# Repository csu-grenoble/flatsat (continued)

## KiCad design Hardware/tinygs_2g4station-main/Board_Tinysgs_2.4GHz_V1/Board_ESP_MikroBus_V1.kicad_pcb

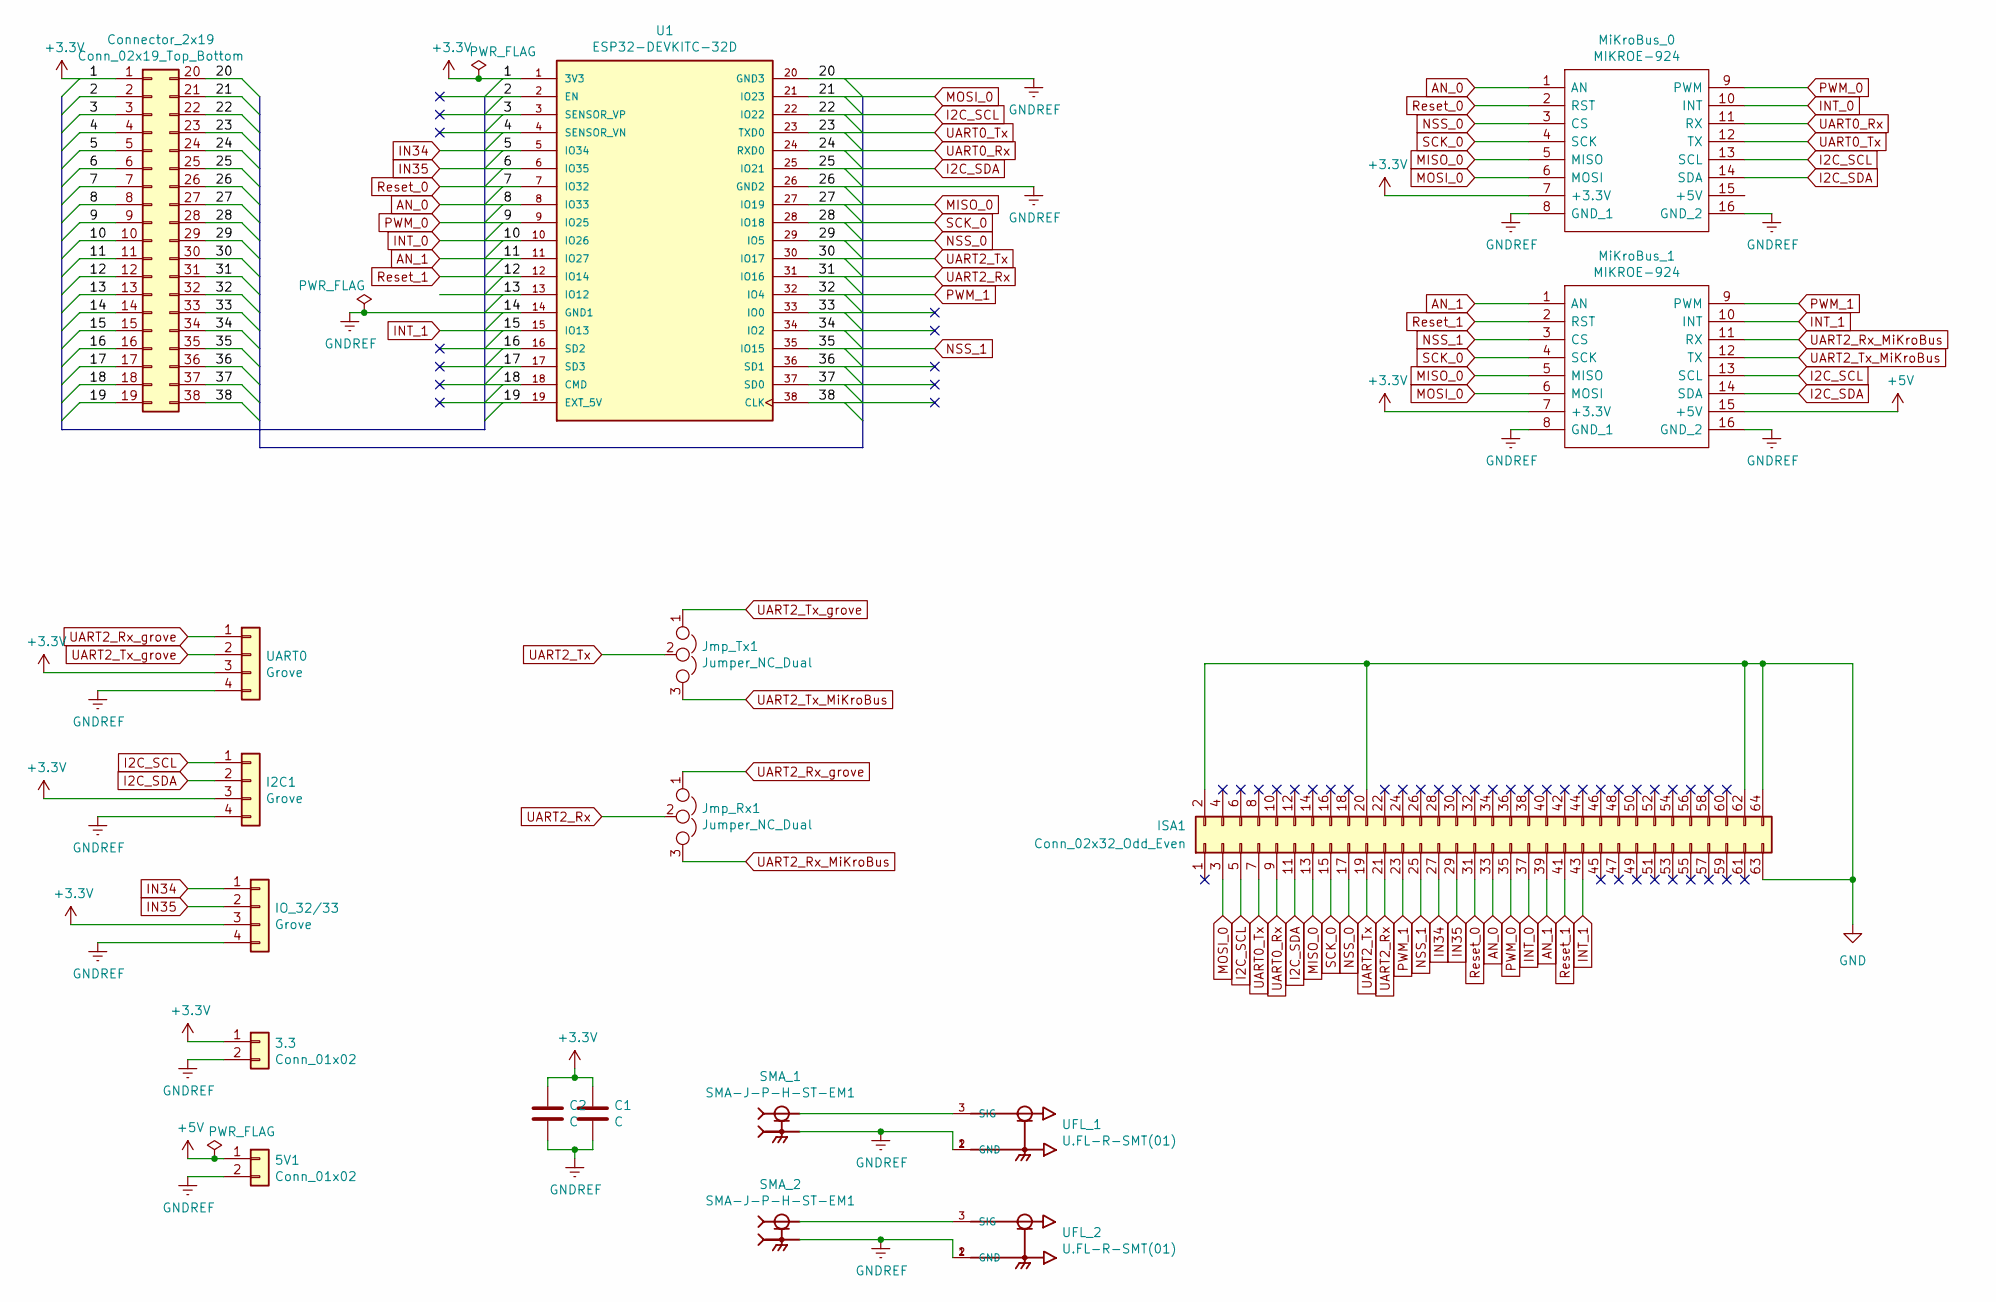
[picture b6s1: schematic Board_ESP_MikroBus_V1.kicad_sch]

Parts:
3.3, 5V1: Conn_01x02; PinHeader_1x02_P2.54mm_Vertical
C1: C; PinHeader_1x02_P2.54mm_Vertical
C2: C; C_0805_2012Metric_Pad1.18x1.45mm_HandSolder
Connector_2x19: Conn_02x19_Top_Bottom; conn_2x19_2.54mm_top_bot
I2C1: Grove; Grove_4pin-2.00mm
IO_32/33: Grove; Grove_4pin-2.00mm
ISA1: Conn_02x32_Odd_Even; PinSocket_2x32_P2.54mm_Vertical
Jmp_Rx1: Jumper_NC_Dual; PinHeader_1x03_P2.54mm_Vertical
Jmp_Tx1: Jumper_NC_Dual; PinHeader_1x03_P2.54mm_Vertical
MiKroBus_0, MiKroBus_1: MIKROE-924; MIKROE924; Manufacturer_Part_Number MIKROE-924; Mouser Part Number 932-MIKROE-924
SMA_1, SMA_2: SMA-J-P-H-ST-EM1; SAMTEC_SMA-J-P-H-ST-EM1; PARTREV G
U1: ESP32-DEVKITC-32D; MODULE_ESP32-DEVKITC-32D; PARTREV 4
UART0: Grove; Grove_4pin-2.00mm
UFL_1, UFL_2: U.FL-R-SMT(01); HRS_U.FL-R-SMT(01)

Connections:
+3V3: 3.3.1, C1.1, C2.1, Connector_2x19.1, I2C1.3, IO_32/33.3, MiKroBus_0.7 (+3.3V), MiKroBus_1.7 (+3.3V), U1.1 (3V3), UART0.3
+5V: 5V1.1, MiKroBus_1.15 (+5V)
/2: Connector_2x19.2, U1.2 (EN)
/3: Connector_2x19.3, U1.3 (SENSOR_VP)
/4: Connector_2x19.4, U1.4 (SENSOR_VN)
/13: Connector_2x19.13, U1.13 (IO12)
/16: Connector_2x19.16, U1.16 (SD2)
/17: Connector_2x19.17, U1.17 (SD3)
/18: Connector_2x19.18, U1.18 (CMD)
/19: Connector_2x19.19, U1.19 (EXT_5V)
/33: Connector_2x19.33, U1.33 (IO0)
/34: Connector_2x19.34, U1.34 (IO2)
/36: Connector_2x19.36, U1.36 (SD1)
/37: Connector_2x19.37, U1.37 (SD0)
/38: Connector_2x19.38, U1.38 (CLK)
AN_0: Connector_2x19.8, ISA1.33, MiKroBus_0.1 (AN), U1.8 (IO33)
AN_1: Connector_2x19.11, ISA1.39, MiKroBus_1.1 (AN), U1.11 (IO27)
GND: ISA1.2, ISA1.20, ISA1.62, ISA1.63, ISA1.64
GNDREF: 3.3.2, 5V1.2, C1.2, C2.2, Connector_2x19.14, Connector_2x19.20, Connector_2x19.26, I2C1.4, IO_32/33.4, MiKroBus_0.8 (GND_1), MiKroBus_0.16 (GND_2), MiKroBus_1.8 (GND_1), MiKroBus_1.16 (GND_2), SMA_1.2_1, SMA_1.2_2, SMA_1.3_1, SMA_1.3_2, SMA_2.2_1, SMA_2.2_2, SMA_2.3_1, SMA_2.3_2, U1.14 (GND1), U1.20 (GND3), U1.26 (GND2), UART0.4, UFL_1.1 (GND), UFL_1.2 (GND), UFL_2.1 (GND), UFL_2.2 (GND)
I2C_SCL: Connector_2x19.22, I2C1.1, ISA1.5, MiKroBus_0.13 (SCL), MiKroBus_1.13 (SCL), U1.22 (IO22)
I2C_SDA: Connector_2x19.25, I2C1.2, ISA1.11, MiKroBus_0.14 (SDA), MiKroBus_1.14 (SDA), U1.25 (IO21)
IN34: Connector_2x19.5, IO_32/33.1, ISA1.27, U1.5 (IO34)
IN35: Connector_2x19.6, IO_32/33.2, ISA1.29, U1.6 (IO35)
INT_0: Connector_2x19.10, ISA1.37, MiKroBus_0.10 (INT), U1.10 (IO26)
INT_1: Connector_2x19.15, ISA1.43, MiKroBus_1.10 (INT), U1.15 (IO13)
MISO_0: Connector_2x19.27, ISA1.13, MiKroBus_0.5 (MISO), MiKroBus_1.5 (MISO), U1.27 (IO19)
MOSI_0: Connector_2x19.21, ISA1.3, MiKroBus_0.6 (MOSI), MiKroBus_1.6 (MOSI), U1.21 (IO23)
NSS_0: Connector_2x19.29, ISA1.17, MiKroBus_0.3 (CS), U1.29 (IO5)
NSS_1: Connector_2x19.35, ISA1.25, MiKroBus_1.3 (CS), U1.35 (IO15)
unnamed: SMA_1.1, UFL_1.3 (SIG)
unnamed: SMA_2.1, UFL_2.3 (SIG)
PWM_0: Connector_2x19.9, ISA1.35, MiKroBus_0.9 (PWM), U1.9 (IO25)
PWM_1: Connector_2x19.32, ISA1.23, MiKroBus_1.9 (PWM), U1.32 (IO4)
Reset_0: Connector_2x19.7, ISA1.31, MiKroBus_0.2 (RST), U1.7 (IO32)
Reset_1: Connector_2x19.12, ISA1.41, MiKroBus_1.2 (RST), U1.12 (IO14)
SCK_0: Connector_2x19.28, ISA1.15, MiKroBus_0.4 (SCK), MiKroBus_1.4 (SCK), U1.28 (IO18)
UART0_Rx: Connector_2x19.24, ISA1.9, MiKroBus_0.11 (RX), U1.24 (RXD0)
UART0_Tx: Connector_2x19.23, ISA1.7, MiKroBus_0.12 (TX), U1.23 (TXD0)
UART2_Rx: Connector_2x19.31, ISA1.21, Jmp_Rx1.2, U1.31 (IO16)
UART2_Rx_MiKroBus: Jmp_Rx1.3, MiKroBus_1.11 (RX)
UART2_Rx_grove: Jmp_Rx1.1, UART0.1
UART2_Tx: Connector_2x19.30, ISA1.19, Jmp_Tx1.2, U1.30 (IO17)
UART2_Tx_MiKroBus: Jmp_Tx1.3, MiKroBus_1.12 (TX)
UART2_Tx_grove: Jmp_Tx1.1, UART0.2

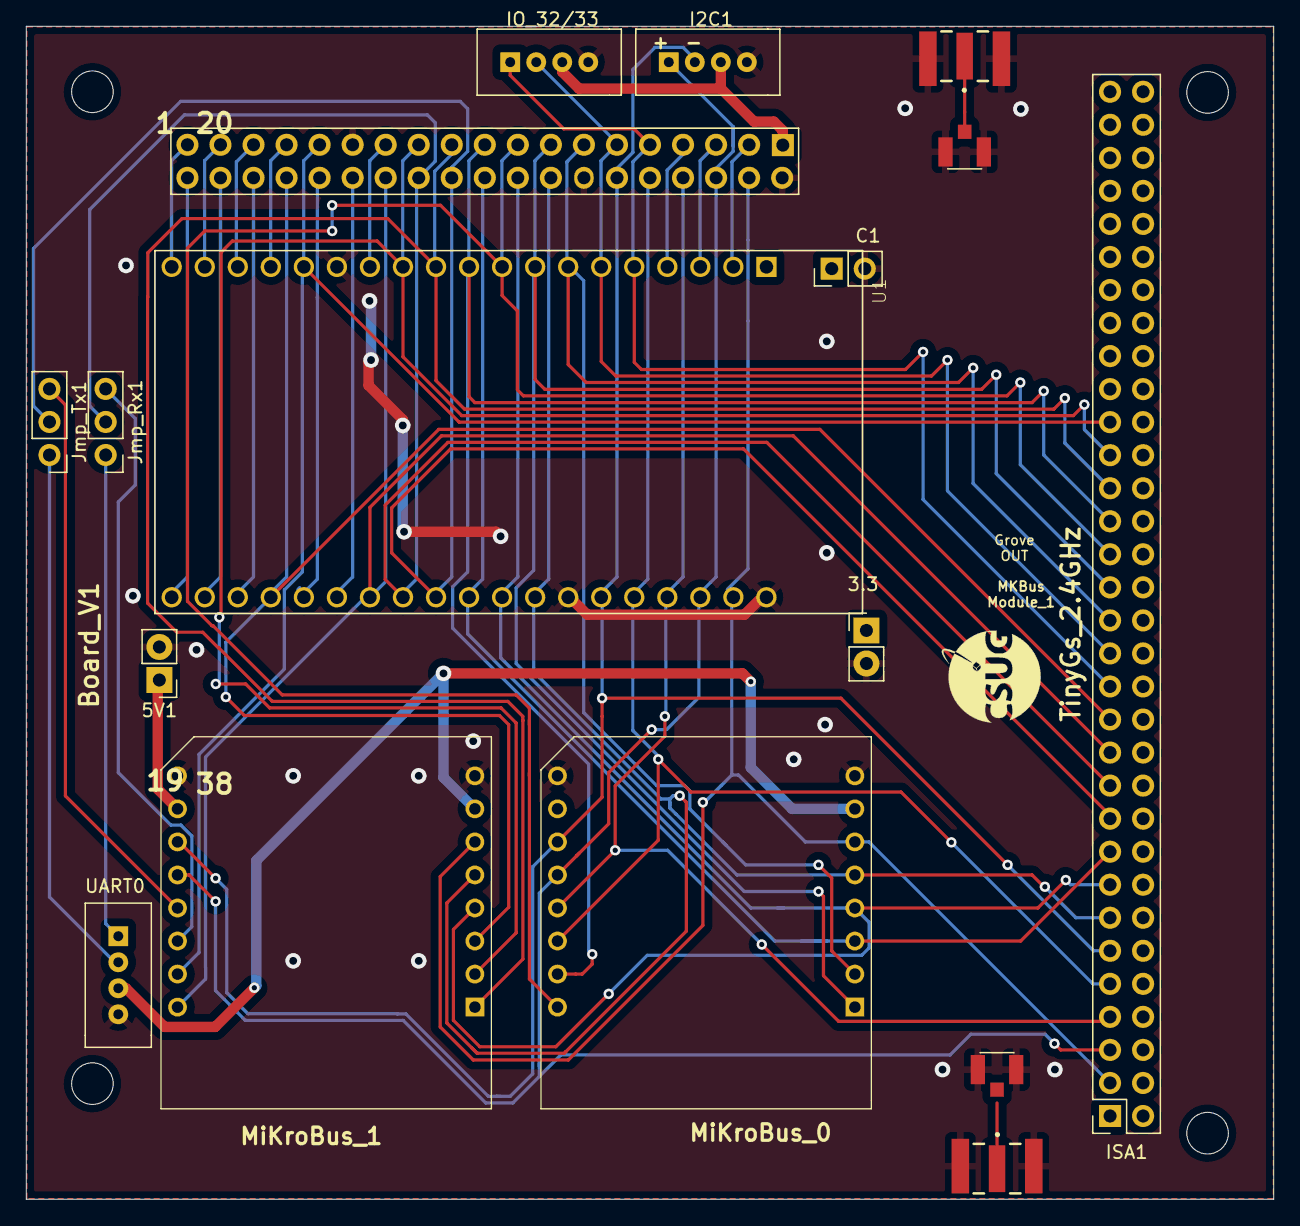
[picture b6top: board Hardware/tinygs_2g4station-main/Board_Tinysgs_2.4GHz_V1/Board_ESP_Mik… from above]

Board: 2 copper layers, 95.9 x 90.2 mm, 18 parts (1 on the bottom side), 44 nets.

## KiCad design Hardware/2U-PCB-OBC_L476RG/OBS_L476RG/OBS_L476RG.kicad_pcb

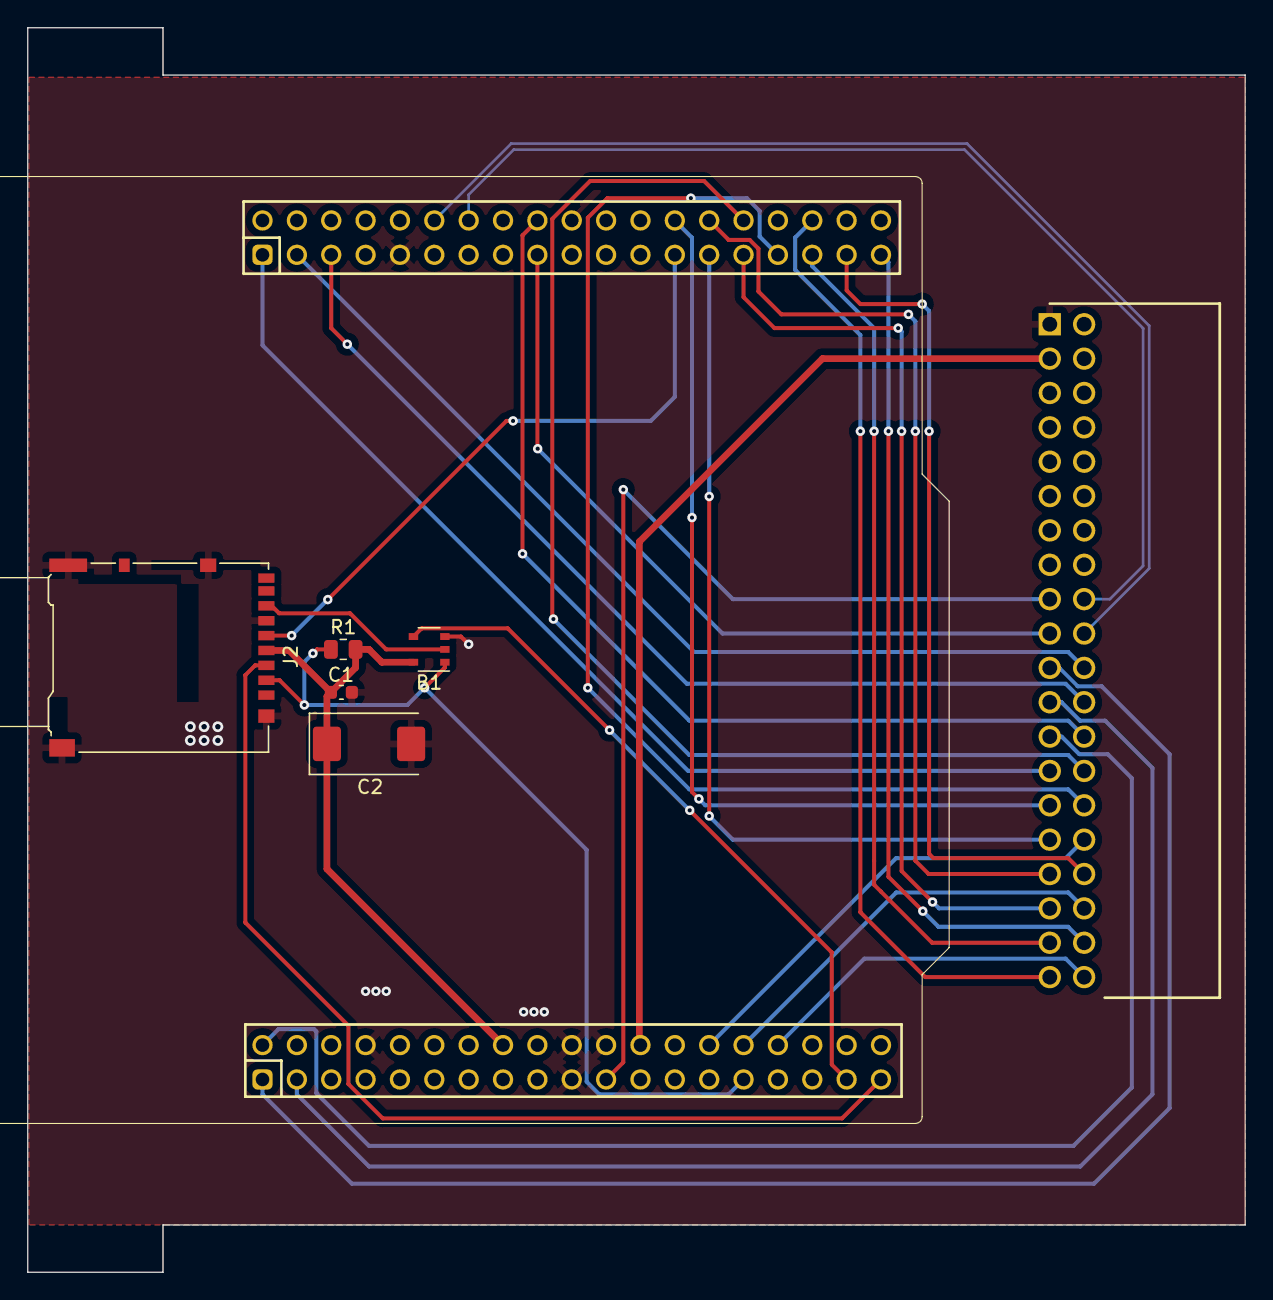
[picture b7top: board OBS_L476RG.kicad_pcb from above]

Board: 2 copper layers, 90.0 x 92.0 mm, 7 parts (0 on the bottom side), 32 nets.

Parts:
B1: TSOP-5_1.65x3.05mm_P0.95mm
C1: 0.1uF; C_0603_1608Metric
C2: 47uF; CP_EIA-7343-31_Kemet-D
J1: Bus Standard; flatsat_conn
J2: Micro_SD_Card_Det_Hirose_DM3AT; microSD_HC_Hirose_DM3AT-SF-PEJM5
R1: 10K; R_0805_2012Metric
U2: NUCLEO_L476RG; Nucleo64

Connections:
+3.3V: B1.5 (VCC), C1.1, C2.1, J2.4 (VDD), R1.2, U2.16 (+3V3)
/CAN_rd: J1.22 (RD), U2.41 (PB8)
/CAN_td: J1.24 (TD), U2.43 (PB9)
/CS: B1.1 (OE), J2.2 (DAT3/CD), R1.1, U2.29 (PH0)
/DAT0: B1.2 (A), J2.7 (DAT0)
/MISO: J1.25 (MISO), U2.2 (PC11)
/MOSI: J1.23 (MOSI), U2.3 (PC12)
/P15: J1.29 (AI_1), U2.64 (PB15)
/P16: J1.31 (AI_2), U2.65 (PB4)
/P17: J1.33 (AI_3), U2.66 (PB14)
/P18: J1.35 (AI_4), U2.67 (PB5)
/P19: J1.37 (AI_5), U2.71 (PA10)
/P20: J1.39 (AI_6), U2.72 (PC4)
/P21: J1.40 (PWM_O_6), U2.32 (PA4)
/P22: J1.38 (PWM_O_5), U2.75 (PA3)
/P23: J1.36 (PWM_O_4), U2.30 (PA1)
/P24: J1.34 (PWM_O_3), U2.73 (PA2)
/P25: J1.32 (PWM_O_2), U2.28 (PA0)
/P26: J1.30 (PWM_O_1), U2.69 (PB3)
/SCK: J1.21 (SCK), U2.1 (PC10)
/SCL/TX_1: J1.19 (TX/SCL), U2.55 (PB6)
/SCL/TX_2: J1.28 (SCL/TX), U2.68 (PB13)
/SDA/RX_1: J1.17 (RX/SDA), U2.21 (PB7)
/SDA/RX_2: J1.26 (SDA/RX), U2.56 (PB11)
/SD_MISO: B1.4 (Y), U2.35 (PC2)
/SD_MOSI: J2.3 (CMD), U2.37 (PC3)
/SD_SCK: J2.5 (CLK), U2.63 (PB10)
/SSEL: J1.27 (SSEL), U2.39 (PC9)
/USB_D+: J1.20 (D+), U2.50 (PA12)
/USB_D-: J1.18 (D-), U2.52 (PA11)
/Vin: J1.3 (V_IN), U2.24 (VIN)
GND: B1.3 (GND), C1.2, C2.2, J1.1 (GND), J2.6 (VSS), J2.11 (SHIELD), U2.8 (GND), U2.19 (GND), U2.20 (GND), U2.22 (GND), U2.47 (GND), U2.58 (GND)

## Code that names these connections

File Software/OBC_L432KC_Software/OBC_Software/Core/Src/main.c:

/********************** INCLUDES *********************************/
#include <Port_Conf.h>
#include "stm32l4xx.h"

#include "main.h"

#include "../CSUG-library/Inc/I2C.hpp"
#include "Clocks.h"
#include "code_eleve.h"
#include "PWM.h"
#include "Timer.h"
#include "UART.h"

/********************** VARIABLES *********************************/


/********************** CODE *********************************/


/*
 * PA9 -> I2C_SCL
 * PA10 -> I2C_SDA
 *
 * PA12 -> CAN1_TD
 * PA11 -> CAN1_RD
 *
 * PB7 -> UART1_RX
 * PB6 -> UART1_TX
 */

int main(void)
{
	//Init clock and flash
	SystemInit();

	ClockConfiguration(); //must do a function setting the clock's source and setting the prescaler of HCLK, PCLK1 & PCLK2

	SetClocks();	//must do a function to set peripherals clocks

	InitPeripheral();		// Init peripheral I/O's
	InitTimer_1();			//init timer 1
	I2C_Init();			//init I2C mode
	while (1)
	{


	}

}

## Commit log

2023-05-09 J'ajoute deux fichiers, un pour kicad et outre pour les codes. J'ajoute aussi le programme pour tester la carte du calculateur
2023-05-11 Adding the tinygs repo
2023-05-11 Here is a version with the ISA connector standard. The schematic is ready, but the layout needs to be fixed
2023-05-12 In this branch there will be some alternative routing that isn't useful for now but for the future it may helps
2023-05-12 Uart groove repositioned
2023-05-12 Nothing really changed, just a wire position fixed
2023-05-12 The TinyGS in cubesat standard with ISA communication is done, all the wires are branched. Verification needed to ensure it's functionality and noise/EM immunity
2023-05-15 Library of esp32 dev kit and PCIe
2023-05-15 We need some changes in the PCIe connector
2023-05-15 Some path tables updated
2023-05-16 Some libs were made and added to schematic, the schematic is almost ready, fixing some warnings
2023-05-17 The base of schematic is completly connected, there is no error, no warning neither by ERC. After some debug connector will be added to give access to some critic connections points, like UART and ot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
2023-05-17 Communication debug grooves were added. Some reset jumpers also
2023-05-17 Footprint assignement is done
2023-05-17 Jumpers for esp32 were changed for splited 1x19.
2023-05-17 Components still in process of placement
2023-05-17 Some libs were added
2023-05-17 Backups commit
2023-05-19 Design changed
2023-05-19 Some changes in footprint and capacitors value
2023-05-22 Model is ready. We must revise
2023-05-26 Remove TinyGS directory
2023-05-26 Silk screen is up to date
2023-05-30 mechanical dimension adjusted, routes retraced.
2023-05-30 Mechanical dim adjusted, verification is needed
2023-05-31 The reset jumpers were changed the footprint for a push button.
2023-06-01 Last changes for ESP32
2023-06-02 This version of corecell and esp32 has somme errors, like power pins and we need to erase the BC543
2023-06-02 Errors in power source and in BC542
2023-06-02 First commit. The schematic must be revised
2023-06-05 New itens added to library, such as BUS from flatsat and the schematic of Nucleo.
2023-06-06 L9616 in the library. This version we still have the GPS signal. From now on I'll let the main withou the GPS signals, because the sensor cards have already one GPS.
2023-06-06 This version also has no GPS I2C labe, nor USB, that has no prevision for use in this version at least.
2023-06-06 Resistors number fixed. Schematic is ready to start routing. Some power routings are done.
2023-06-06 Firt commit
2023-06-09 Some itens were added
2023-06-09 The board is ready. Some verifications required
2023-06-12 Project name was wrong in in kicad files. Project renamed
2023-06-12 Differential pair impedance balanced
2023-06-12 adding BOM
2023-06-12 Removed ODS file
2023-06-12 BOM changed
2023-06-12 position and gerber files
2023-06-14 Some libraries were added for NAND gate. Also I2C in mikrobus changed. ROuting started respecting constraints.
2023-06-15 Traces almost ready, I'm avoiding through holes because it will be done in campus, not with specialized machines. Constraints: 125 um clearence and wire size. It will be not possible completly avoid 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
2023-06-20 New library joined, cause we changed for a 7404 logic gate. All the routes were re-made.
2023-06-21 The board is ready, need some revision
2023-06-27 First version for fabrication
2023-06-27 TinyGS in 2u format.
2023-06-30 Selection CAN juper added. Can buffer added
2023-07-03 Everything must be in C. So files were changed, and the IO ports were setted
2023-07-06 Images and sch_pdf changed
2023-07-07 Spreedshit of the I2C timing calculus and registers configuration
2023-07-07 The I2C initialization is ready. Now I'm in address configuration
2023-07-07 Commit for small changes
2023-07-10 I2C firmware almost ready. Haven't tried to build this code yet. There maybe errors in this code
2023-07-18 Flatsat connector was in the wrong side. All the routes were remade.
2023-07-18 Flatsat connector was in the wrong side. All routes were remade.
2023-07-18 I2C library has some bugs, but the peripheral library is working fine with clearing masks added.
2023-07-21 Final changes and gerber added
2023-07-21 I2C almost working. The address is working fine, must test the read.
2023-08-23 improve readme
2023-08-23 add ref to images
2023-08-23 add images
2023-08-23 image resizing
2023-08-23 add gitignore
2023-09-13 add sections
2023-11-22 add image
2023-12-18 detail boards components
2024-06-24 push leo
2024-07-11 correction carte Lucas
2024-08-01 reprise de la serigraphie
2024-08-02 peaufinage serigraphie et tracage fichiers de fabrication pour commande JLCPCB
2024-08-26 init dir for protoboard
2024-08-31 Delete Hardware/2U-PCB-Com_Nucleo-L432kC/Com_Nucleo-L432kc/Com_Nucleo-L432kc-backups directory
    delete backup dir
2024-08-31 excludes backup dir
2024-09-02 refactor
2024-09-02 init dir for Arduino firmwares
2024-09-02 init dir for RIOT OS firmwares
2024-09-02 add ref
2024-09-02 add ref to arduino libs
2024-09-02 add libs for test
2024-09-02 add lib for CAN bus
2024-09-02 add sx1302/3
2024-09-02 fix Rak module name
2024-09-02 add ref to https://github.com/EasySpace-Diffusion
2024-09-02 add uBlox M8N
2024-09-02 add uBlox
2024-09-02 add lib for sx1302
2024-09-02 add board with Nucleo 64 (l476rg)
2024-09-03 add basic funtions to test
2024-10-04 remise au propre du projet avant redesign
2024-10-04 début de la reprise de la carte
2024-10-07 schématique terminée
2024-10-07 routage terminé
2024-10-08 ajout documentation
2024-10-08 ajout documentation bis
2024-10-10 ajout trous entretoise pour support mini PCI Express
2024-10-14 fix mauvaise empreinte connecteur
2024-12-03 add section for logiciel
2024-12-04 IMPROVE
2024-12-16 add extra photos
2025-02-06 finalisation Thingsat Inisat v1.0
2025-02-12 fix spec
2025-02-18 fix and improvement
2025-02-18 minor fix
2025-02-18 fix with install
2025-02-18 add misc
2025-02-19 improve readme ; add ref to firmware
2025-02-19 fix bold
2025-02-19 add missing files
2025-02-20 add pinouts for sx1302 and sx1303 modules
2025-02-20 fix ref
2025-02-20 add image for sx1302cssxxxgw1
2025-02-20 add ht1303
2025-02-20 fix ref to Thingsat @ INISAT 📡 🚀
2025-02-20 add ref to sx1302_modules
2025-02-20 add RAK2287
2025-02-21 fix typo
2025-02-22 fix compliance
2025-02-22 rename and move dir
2025-02-22 move images
2025-02-22 improve readme; add images
2025-02-22 change subtitle
2025-02-22 add contributor
2025-02-22 add schematic
2025-03-06 add module lists
2025-03-11 add compatible module
2025-03-26 add compliance for wm1302
2025-03-27 add info for fine timestamping
2025-03-27 improve gitignore
2025-05-19 improve support
2025-05-21 add example for GNSS UART modules
2025-06-11 add adc channels
2025-10-27 add waveshare
2025-10-27 add power consumption
2026-01-14 move directory to https://github.com/thingsat/sx1302_modules
